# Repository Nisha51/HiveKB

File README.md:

**HIVE KB**

A low profile ergo keyboard that uses hexkeycaps

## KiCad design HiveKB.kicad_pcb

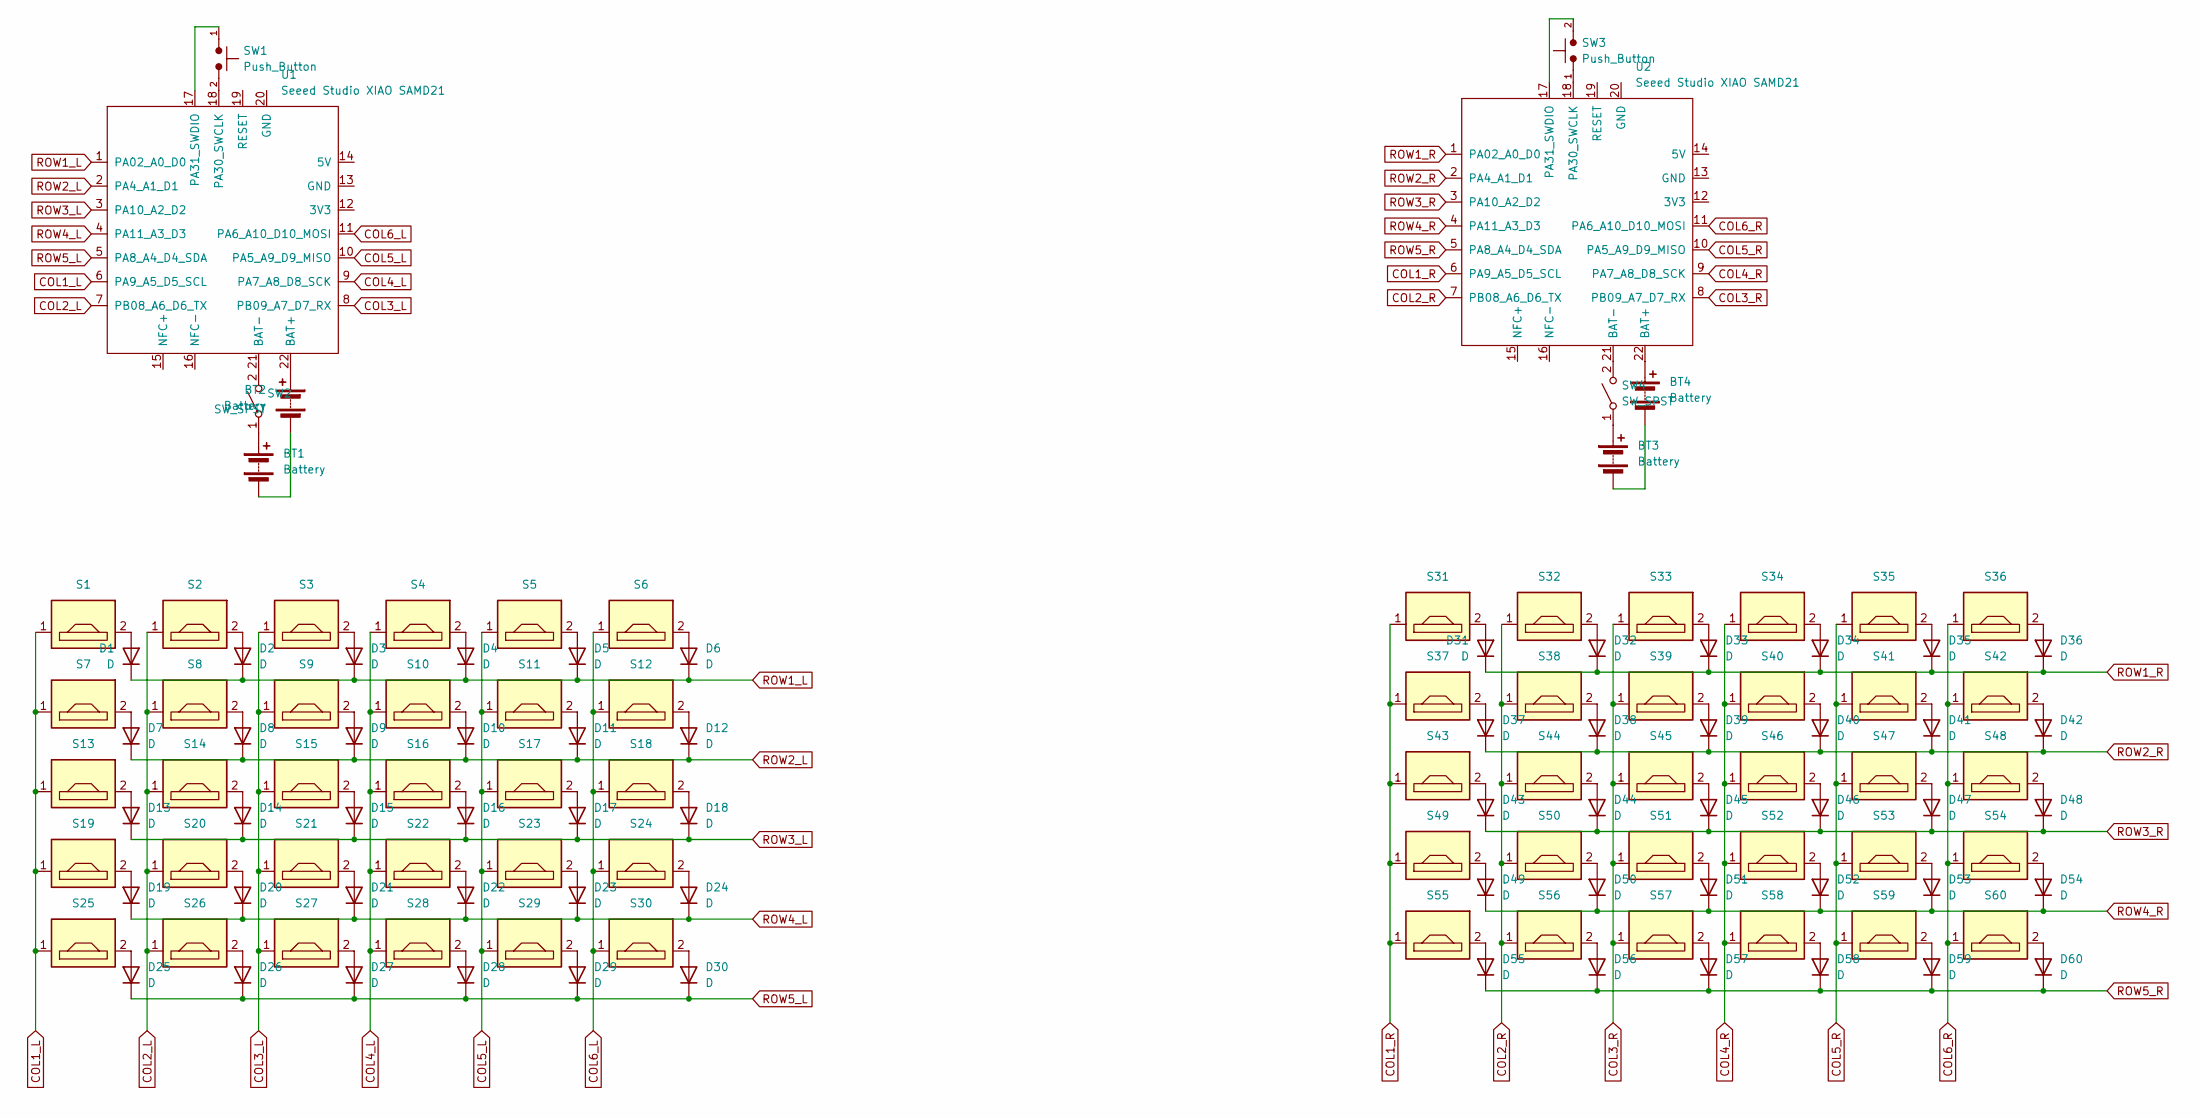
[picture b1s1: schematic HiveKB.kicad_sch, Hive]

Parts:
BT1, BT2, BT3, BT4: Battery
D1, D2, D3, D4, D5, D6, D7, D8, D9, D10, D11, D12, D13, D14, D15, D16, D17, D18, D19, D20, D21, D22, D23, D24, D25, D26, D27, D28, D29, D30, D31, D32, D33, D34, D35, D36, D37, D38, D39, D40, D41, D42, D43, D44, D45, D46, D47, D48, D49, D50, D51, D52, D53, D54, D55, D56, D57, D58, D59, D60: D; D_SOD-123
S1, S2, S3, S4, S5, S6, S7, S8, S9, S10, S11, S12, S13, S14, S15, S16, S17, S18, S19, S20, S21, S22, S23, S24, S25, S26, S27, S28, S29, S30, S31, S32, S33, S34, S35, S36, S37, S38, S39, S40, S41, S42, S43, S44, S45, S46, S47, S48, S49, S50, S51, S52, S53, S54, S55, S56, S57, S58, S59, S60: PG1350; PG1350_hotswap
SW1, SW3: Push_Button; SW_SPST_Omron_B3FS-100xP
SW2, SW4: SW_SPST; SW_SPST_Omron_B3FS-100xP
U1, U2: Seeed Studio XIAO SAMD21; XIAO-nRF52840-Sense-14P-2.54-21X17.8MM

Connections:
COL1_L: S1.1, S7.1, S13.1, S19.1, S25.1, U1.6 (PA9_A5_D5_SCL)
COL1_R: S31.1, S37.1, S43.1, S49.1, S55.1, U2.6 (PA9_A5_D5_SCL)
COL2_L: S2.1, S8.1, S14.1, S20.1, S26.1, U1.7 (PB08_A6_D6_TX)
COL2_R: S32.1, S38.1, S44.1, S50.1, S56.1, U2.7 (PB08_A6_D6_TX)
COL3_L: S3.1, S9.1, S15.1, S21.1, S27.1, U1.8 (PB09_A7_D7_RX)
COL3_R: S33.1, S39.1, S45.1, S51.1, S57.1, U2.8 (PB09_A7_D7_RX)
COL4_L: S4.1, S10.1, S16.1, S22.1, S28.1, U1.9 (PA7_A8_D8_SCK)
COL4_R: S34.1, S40.1, S46.1, S52.1, S58.1, U2.9 (PA7_A8_D8_SCK)
COL5_L: S5.1, S11.1, S17.1, S23.1, S29.1, U1.10 (PA5_A9_D9_MISO)
COL5_R: S35.1, S41.1, S47.1, S53.1, S59.1, U2.10 (PA5_A9_D9_MISO)
COL6_L: S6.1, S12.1, S18.1, S24.1, S30.1, U1.11 (PA6_A10_D10_MOSI)
COL6_R: S36.1, S42.1, S48.1, S54.1, S60.1, U2.11 (PA6_A10_D10_MOSI)
unnamed: BT1.1 (+), SW2.1 (A)
unnamed: BT2.1 (+), U1.22 (BAT+)
unnamed: BT3.1 (+), SW4.1 (A)
unnamed: BT4.1 (+), U2.22 (BAT+)
unnamed: D1.2 (A), S1.2
unnamed: D2.2 (A), S2.2
unnamed: D3.2 (A), S3.2
unnamed: D4.2 (A), S4.2
unnamed: D5.2 (A), S5.2
unnamed: D6.2 (A), S6.2
unnamed: D7.2 (A), S7.2
unnamed: D8.2 (A), S8.2
unnamed: D9.2 (A), S9.2
unnamed: D10.2 (A), S10.2
unnamed: D11.2 (A), S11.2
unnamed: D12.2 (A), S12.2
unnamed: D13.2 (A), S13.2
unnamed: D14.2 (A), S14.2
unnamed: D15.2 (A), S15.2
unnamed: D16.2 (A), S16.2
unnamed: D17.2 (A), S17.2
unnamed: D18.2 (A), S18.2
unnamed: D19.2 (A), S19.2
unnamed: D20.2 (A), S20.2
unnamed: D21.2 (A), S21.2
unnamed: D22.2 (A), S22.2
unnamed: D23.2 (A), S23.2
unnamed: D24.2 (A), S24.2
unnamed: D25.2 (A), S25.2
unnamed: D26.2 (A), S26.2
unnamed: D27.2 (A), S27.2
unnamed: D28.2 (A), S28.2
unnamed: D29.2 (A), S29.2
unnamed: D30.2 (A), S30.2
unnamed: D31.2 (A), S31.2
unnamed: D32.2 (A), S32.2
unnamed: D33.2 (A), S33.2
unnamed: D34.2 (A), S34.2
unnamed: D35.2 (A), S35.2
unnamed: D36.2 (A), S36.2
unnamed: D37.2 (A), S37.2
unnamed: D38.2 (A), S38.2
unnamed: D39.2 (A), S39.2
unnamed: D40.2 (A), S40.2
unnamed: D41.2 (A), S41.2
unnamed: D42.2 (A), S42.2
unnamed: D43.2 (A), S43.2
unnamed: D44.2 (A), S44.2
unnamed: D45.2 (A), S45.2
unnamed: D46.2 (A), S46.2
unnamed: D47.2 (A), S47.2
unnamed: D48.2 (A), S48.2
unnamed: D49.2 (A), S49.2
unnamed: D50.2 (A), S50.2
unnamed: D51.2 (A), S51.2
unnamed: D52.2 (A), S52.2
unnamed: D53.2 (A), S53.2
unnamed: D54.2 (A), S54.2
unnamed: D55.2 (A), S55.2
unnamed: D56.2 (A), S56.2
unnamed: D57.2 (A), S57.2
unnamed: D58.2 (A), S58.2
unnamed: D59.2 (A), S59.2
unnamed: D60.2 (A), S60.2
unnamed: SW2.2 (B), U1.21 (BAT-)
unnamed: SW4.2 (B), U2.21 (BAT-)
unnamed: SW1.2, U1.18 (PA30_SWCLK)
unnamed: SW1.1, U1.17 (PA31_SWDIO)
unnamed: SW3.1, U2.18 (PA30_SWCLK)
unnamed: SW3.2, U2.17 (PA31_SWDIO)
ROW1_L: D1.1 (K), D2.1 (K), D3.1 (K), D4.1 (K), D5.1 (K), D6.1 (K), U1.1 (PA02_A0_D0)
ROW1_R: D31.1 (K), D32.1 (K), D33.1 (K), D34.1 (K), D35.1 (K), D36.1 (K), U2.1 (PA02_A0_D0)
ROW2_L: D7.1 (K), D8.1 (K), D9.1 (K), D10.1 (K), D11.1 (K), D12.1 (K), U1.2 (PA4_A1_D1)
ROW2_R: D37.1 (K), D38.1 (K), D39.1 (K), D40.1 (K), D41.1 (K), D42.1 (K), U2.2 (PA4_A1_D1)
ROW3_L: D13.1 (K), D14.1 (K), D15.1 (K), D16.1 (K), D17.1 (K), D18.1 (K), U1.3 (PA10_A2_D2)
ROW3_R: D43.1 (K), D44.1 (K), D45.1 (K), D46.1 (K), D47.1 (K), D48.1 (K), U2.3 (PA10_A2_D2)
ROW4_L: D19.1 (K), D20.1 (K), D21.1 (K), D22.1 (K), D23.1 (K), D24.1 (K), U1.4 (PA11_A3_D3)
ROW4_R: D49.1 (K), D50.1 (K), D51.1 (K), D52.1 (K), D53.1 (K), D54.1 (K), U2.4 (PA11_A3_D3)
ROW5_L: D25.1 (K), D26.1 (K), D27.1 (K), D28.1 (K), D29.1 (K), D30.1 (K), U1.5 (PA8_A4_D4_SDA)
ROW5_R: D55.1 (K), D56.1 (K), D57.1 (K), D58.1 (K), D59.1 (K), D60.1 (K), U2.5 (PA8_A4_D4_SDA)

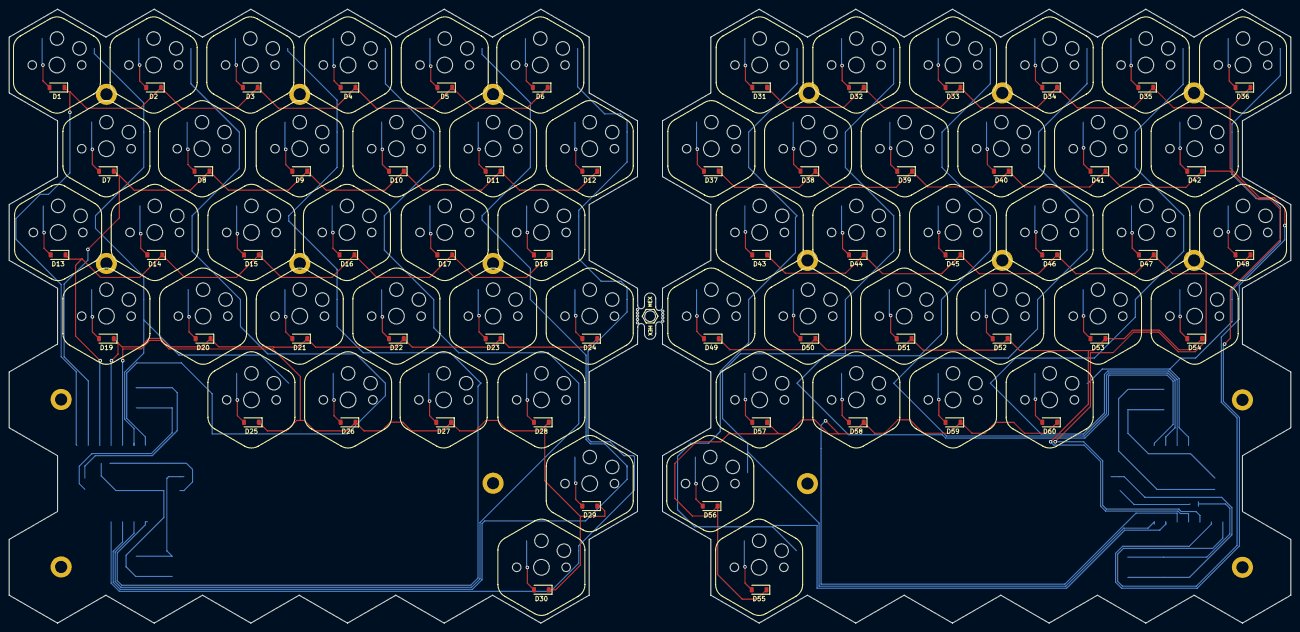
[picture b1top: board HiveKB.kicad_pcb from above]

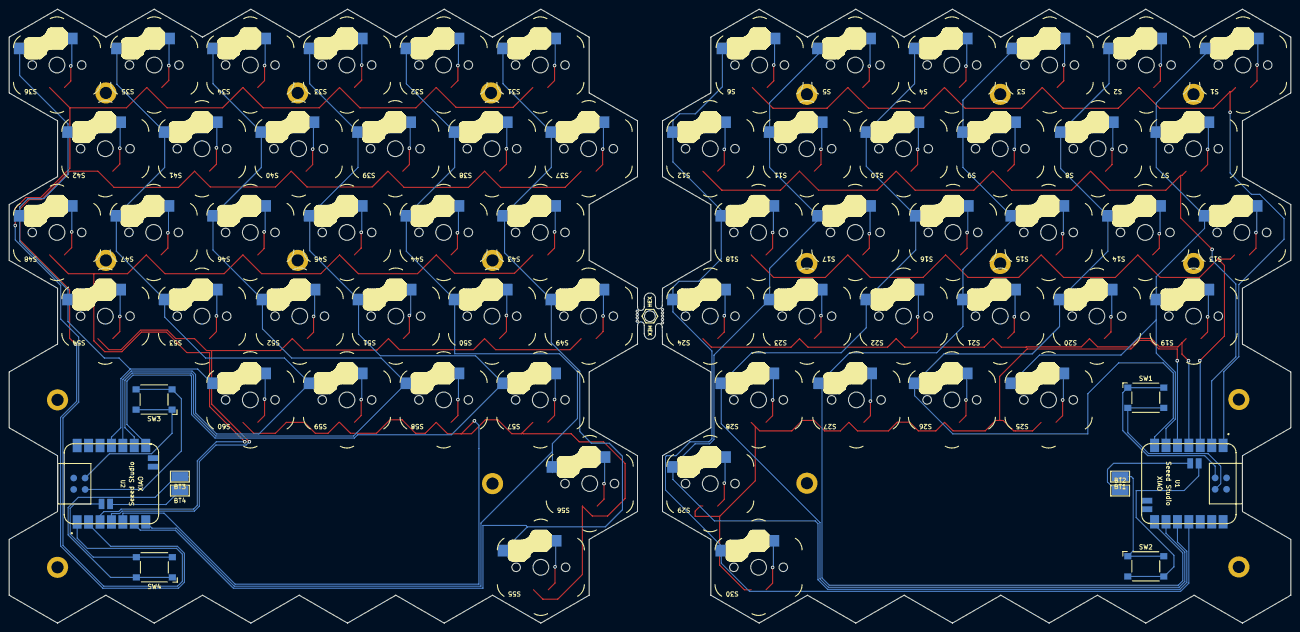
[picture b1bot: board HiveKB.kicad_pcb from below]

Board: 2 copper layers, 285.1 x 136.5 mm, 131 parts (70 on the bottom side), 92 nets.

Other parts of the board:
MB5: 5.5mm; mousebites_5p5mm_easysnap

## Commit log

2023-12-22 Create Kicad
2024-03-14 Uploaded PCB
2024-03-14 Uploaded Libraries
